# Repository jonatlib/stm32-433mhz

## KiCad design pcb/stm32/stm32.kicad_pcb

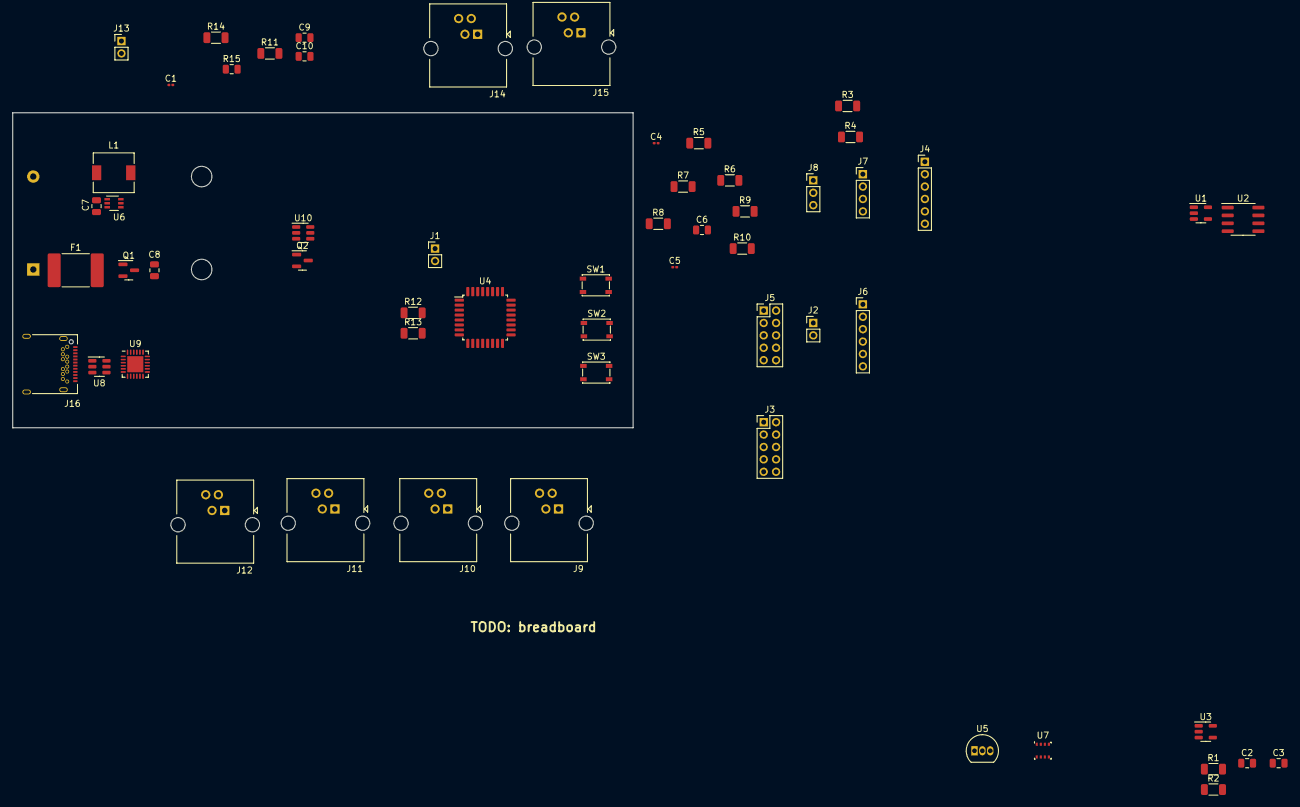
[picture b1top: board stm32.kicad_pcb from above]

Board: 2 copper layers, 100.1 x 50.8 mm, 59 parts (1 on the bottom side), 34 nets, no tracks yet.

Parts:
BT1: Battery; BatteryHolder_Keystone_2462_2xAA
C1: 100n; C_0201_0603Metric
C2, C7, C8, C9: 10u; C_0805_2012Metric
C3, C10: 100n; C_0805_2012Metric
C4, C5: 100nF; C_0201_0603Metric
C6: 1uF; C_0805_2012Metric
F1: Fuse; Fuse_2920_7451Metric_Pad2.10x5.45mm_HandSolder
J1, J2, J13: Conn_01x02_Pin; PinHeader_1x02_P2.00mm_Vertical
J3, J5: Conn_02x05_Top_Bottom; PinHeader_2x05_P2.00mm_Vertical
J4, J6: Conn_01x06_Pin; PinHeader_1x06_P2.00mm_Vertical
J7: Conn_01x04_Pin; PinHeader_1x04_P2.00mm_Vertical
J8: Conn_01x02_Pin; PinHeader_1x03_P2.00mm_Vertical
J9, J10, J11, J12, J14, J15: 4P4C; RJ14_Connfly_DS1133-S4_Horizontal
J16: USB_C_Receptacle; USB_C_Receptacle_Amphenol_12401548E4-2A
L1: 4,7uH; L_6.3x6.3_H3
Q1: ???; SOT-23
Q2: DMG3415; SOT-23
R1, R2, R3, R4, R5, R6, R7, R8, R9: 10K; R_1206_3216Metric
R10: 1K; R_1206_3216Metric
R11: 47k?; R_1206_3216Metric
R12, R13: 500K 1%; R_1206_3216Metric
R14: ?? 1%; R_1206_3216Metric
R15: ?? 1%; C_0805_2012Metric
SW1, SW2, SW3: SW_Push; SW_SPST_PTS810
U1: 24AA02-OT; SOT-23-5
U2: 23A256; SOIC-8_3.9x4.9mm_P1.27mm
U3: TPS2041B; SOT-23-5
U4: STM32G070KBT6; LQFP-32_7x7mm_P0.8mm
U5: DS18B20; TO-92_Inline
U6: TPS61222DCK; Texas_R-PDSO-G6
U7: BME280; Bosch_LGA-8_2.5x2.5mm_P0.65mm_ClockwisePinNumbering
U8: USBLC6-4SC6; SOT-23-6
U9: CP2102N-Axx-xQFN24; QFN-24-1EP_4x4mm_P0.5mm_EP2.6x2.6mm
U10: TPL5110; SOT-23-6

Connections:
5V_Enable: J3.4, R11.1, U4.15 (PB0-GPIO_Output), U6.6 (EN)
+3.3V: C1.1, C4.1, C6.1, C8.1, J1.1, J1.2, J2.1, J4.1, J6.1, J7.1, J8.1, J13.1, Q1.2 (S), R1.1, R2.1, R3.1, R4.1, R5.2, R9.1, R12.1, SW1.1, SW2.1, U1.4 (V_{CC}), U2.7 (~HOLD), U2.8 (VCC), U3.5 (IN), U4.4 (VDD)
+5V: C9.1, C10.1, R14.1, U6.4 (VOUT)
/power_supply/VBAT_SENSE: R12.2, R13.1, U4.12 (PA5-ADC1_IN5)
BOOT0: J5.8, J6.2, R8.1, SW2.2, U4.25 (PA14-BOOT0-SYS_SWCLK)
GND: BT1.2 (-), C1.2, C2.2, C3.2, C4.2, C5.2, C6.2, C7.2, C8.2, C9.2, C10.2, J3.5, J3.10, J4.6, J5.2, J5.7, J6.3, J7.4, J8.3, Q1.1 (G), R6.2, R7.2, R8.2, R11.2, R13.2, R15.2, SW3.2, U1.2 (V_{SS}), U1.5 (WP), U2.4 (VSS), U3.2 (GND), U4.5 (VSS), U6.3 (GND)
I2C_SCL: J3.8, J7.3, R4.2, U1.1 (SCL), U4.30 (PB6-I2C1_SCL)
I2C_SDA: J3.3, J7.2, R3.2, U1.3 (SDA), U4.1 (PB9-I2C1_SDA)
unnamed: C7.1, J13.2, L1.1, U6.1 (VIN)
unnamed: BT1.1 (+), F1.1
unnamed: J2.2, J5.4, J5.9
unnamed: J16.A1 (GND), J16.A12 (GND), J16.B1 (GND), J16.B12 (GND)
unnamed: J16.A4 (VBUS), J16.A9 (VBUS), J16.B4 (VBUS), J16.B9 (VBUS)
unnamed: F1.2, Q1.3 (D)
unnamed: R10.2, SW3.1
unnamed: R2.2, U3.3 (~OC)
unnamed: R14.2, R15.1, U6.2 (FB)
unnamed: L1.2, U6.5 (L)
unnamed: U9.2 (GND), U9.25 (GND)
OneWire: J3.7, R5.1, U4.18 (PA8-GPIO_Output)
RF_RX: J3.1, U4.2 (PC14-OSC32_IN-GPIO_EXTI14)
RF_TX: J3.6, U4.3 (PC15-OSC32_OUT-GPIO_EXTI15)
SENSOR_VDD: C2.1, C3.1, U3.1 (OUT)
SEN_ENABLE: J3.9, R1.2, U3.4 (~EN), U4.16 (PB1-GPIO_Output)
SPI_MISO: J4.3, U2.2 (Q), U4.22 (PA11PA9-SPI1_MISO)
SPI_MOSI: J4.4, U2.5 (D), U4.23 (PA12PA10-SPI1_MOSI)
SPI_SCK: J4.2, U2.6 (C), U4.8 (PA1-SPI1_SCK)
SPI_SS1: U2.1 (~S), U4.13 (PA6-ADC1_IN6)
SPI_SS2: J4.5, U4.14 (PA7-ADC1_IN7)
SWD_IO: J5.6, J6.4, U4.24 (PA13-SYS_SWDIO)
SWD_RESET: C5.1, J5.1, J6.5, R9.2, R10.1, U4.6 (PF2-NRST)
Sleep_Enable: J3.2, U4.17 (PB2-GPIO_Output)
WAKEUP_1: R7.1, U4.7 (PA0-SYS_WKUP1)
WAKEUP_2: J8.2, R6.1, SW1.2, U4.11 (PA4-SYS_WKUP2)

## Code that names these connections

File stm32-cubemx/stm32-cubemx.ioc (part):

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Mcu.Name=STM32G070KBTx
Mcu.Package=LQFP32
Mcu.UserName=STM32G070KBTx
PA0.Mode=SYS_WakeUp0
PA0.Signal=SYS_WKUP1
PA1.Mode=Full_Duplex_Master
PA1.Signal=SPI1_SCK
PA10.Mode=Asynchronous
PA10.Signal=USART1_RX
PA11\ [PA9].Mode=Full_Duplex_Master
PA11\ [PA9].Signal=SPI1_MISO
PA12\ [PA10].Mode=Full_Duplex_Master
PA12\ [PA10].Signal=SPI1_MOSI
PA13.Mode=Serial_Wire
PA13.Signal=SYS_SWDIO
PA14-BOOT0.Mode=Serial_Wire
PA14-BOOT0.Signal=SYS_SWCLK
PA4.Mode=SYS_WakeUp1
PA4.Signal=SYS_WKUP2
PA5.Mode=IN5
PA5.Signal=ADC1_IN5
PA6.Mode=IN6
PA6.Signal=ADC1_IN6
PA7.Mode=IN7
PA7.Signal=ADC1_IN7
PA8.Signal=GPIO_Output
PA9.Mode=Asynchronous
PA9.Signal=USART1_TX
PB0.Signal=GPIO_Output
PB1.Signal=GPIO_Output
PB2.Signal=GPIO_Output
PB6.Mode=I2C
PB6.Signal=I2C1_SCL
PB9.Mode=I2C
PB9.Signal=I2C1_SDA
PC14-OSC32_IN\ (PC14).Signal=GPXTI14
PC15-OSC32_OUT\ (PC15).Signal=GPXTI15
RCC.HSE_VALUE=8000000
RCC.SYSCLKFreq_VALUE=16000000
board=custom

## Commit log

2023-02-04 Better timing handling
2023-02-04 Generic writer and reader
2023-02-04 Cleanup
2023-02-04 Added base reader and writer
2023-02-05 Transport writer working
2023-02-05 Work on packet builder and codec
2023-02-06 Prepared receiving transport
2023-02-06 Renamed address fields not to be confusing
2023-02-06 Implementing window
2023-02-06 Optimistics receiving done
2023-02-06 Simple receiver
2023-02-06 Preparing main structure
2023-02-06 Clippy fixes
2023-02-06 Clippy errors
2023-02-06 Some changes and working reader
2023-02-06 Removed unused traces
2023-02-06 Timing and comments
2023-02-07 Some more comments and cleanups
2023-02-07 Working on HW layer
2023-02-07 Added HAL and builder
2023-02-07 How to resolve the strong reference?
2023-02-07 Linting errors
2023-02-07 It compiles!
2023-02-07 Sending struct
2023-02-07 Added proper sequence numbers
2023-02-07 Prepare for resend
2023-02-08 Moved sequence numbers to a different module
2023-02-08 Working on sequence numbers tests
2023-02-08 WIP ordering
2023-02-08 More tests
2023-02-09 Command for local test
2023-02-09 Finally sequence number working
2023-02-09 Sequence numbers done
2023-02-09 Window implemented using new sequence numbers
2023-02-09 Sorting in window
2023-02-09 Enable resend again
2023-02-09 Main cleanup
2023-02-09 Resend working
2023-02-10 Added create i2c bus
2023-02-10 Updated compile flags
2023-02-10 Testing shorter timing
2023-02-12 Preparing manufacturing
2023-02-13 Adding sensor dependencies
2023-02-13 Preparing schema
2023-02-13 Fixed schema
2023-02-14 Upgrade to kicad7
2023-02-14 Prepared labels for MCU
2023-02-15 PCB update
2023-02-17 PCB stuff
2023-02-17 Slow progress
2023-02-17 Updated PCB
2023-02-19 Update pcb
2023-02-20 Preparing new codecs
2023-02-20 WIP reed solomon
2023-02-20 Dynamic size for codec
2023-02-20 Reed solomon codec
2023-02-20 Using different codec
2023-02-21 Const reed solomon buffer size
2023-02-21 Reed solomon buffers are now generic
2023-02-21 RS tests
2023-02-21 Preparing chaining
2023-02-21 Support for codec errors
2023-02-21 Chain WIP
2023-02-21 Codecs
2023-02-21 WIP compression
2023-02-21 Fixed compression
2023-02-22 WIP compression in writer
2023-02-22 Finished compression in writer side
2023-02-22 Use reedsolomon and compression in main
2023-02-22 Support decompression
2023-02-22 Make it compilable
2023-02-22 Implemented chaining
2023-02-22 Four to six bits
2023-02-22 Use RS and 4/6 codec at the same time
2023-02-22 Some fixes on HW
2023-02-25 Playing with memoery
2023-02-25 Added all hiearchical labels
2023-02-26 Updated in memory
2023-02-26 Prepare for other components
2023-02-27 More work on memory
2023-02-27 Refactor modules
2023-02-27 Dummy memory
2023-02-27 Test
2023-02-28 WIP allocator
2023-02-28 Generic memory
2023-02-28 FIX memory typing
2023-02-28 Screw generic memory
2023-02-28 Dummy executor
2023-02-28 Tests for box
2023-02-28 Testing custom box
2023-02-28 Added available memory fns
2023-02-28 Allocator fixes
2023-02-28 Collapse
2023-03-01 Collapsing
2023-03-01 Fixed lifetimes
2023-03-01 Support for generic cold array
2023-03-01 Renamed to ColdBox
2023-03-01 WIP vec
2023-03-01 Moved boxed to more modules
2023-03-01 API to work with smaller memory then allocated
2023-03-01 Array access on box
2023-03-01 Cold vec
2023-03-02 Small fixes
2023-03-03 Power supply
2023-03-03 Vec progress
2023-03-03 From iterator
2023-03-03 Moved PCB forwar
2023-03-03 Packages
2023-03-03 PCB testing
2023-03-06 VDD supply added
2023-03-06 PCB updates
2023-03-06 PWR comment
2023-03-07 updated power supply comment
2023-03-07 PCB in progress
2023-03-07 Progress
2023-03-08 Setup board
2023-03-08 Setup traces
2023-03-08 Updated tracks in PCB
2023-03-09 Small work on pcb
2023-03-09 Global allocator
2023-03-09 Support from iter in vec with global allocator
2023-03-10 unsafe sync on dummy allocator for testing
2023-03-10 Added test for from iter
2023-03-10 Fixing global allocator
2023-03-13 Testing the allocator memory addresses
2023-03-13 Fixed from iter
2023-03-14 Fixing global allocator init
2023-03-14 Moved global alloc tests
2023-03-17 WIP pcb
2023-04-07 Small update
2023-04-08 Added todos
2023-04-11 Renamed PWM reader and writer
2023-04-11 WIP manchester
2023-04-11 Moved all pwm physical layer under under submodule
2023-04-11 Clippy for external memory
2023-04-11 Clippy base fixes
2023-04-11 Renamed bit_io to physical_layer
2023-04-11 update schema
2023-04-12 Small updates on pcb
2023-06-01 Fixing for new version of rust
2023-06-02 Preparing separated sync
2023-06-03 Prearing syncing
2023-06-06 Removed wrong RefCells
2023-06-06 WIP container for clonning
2023-06-07 WIP shared
2023-06-07 WIP shared pin
2023-06-07 Finished shared pin for readers
2023-06-07 Implemnted shared output and sync writer
2023-06-08 Starting manchester
2023-06-08 WIP manchester read
2023-06-09 Finished a weird manchester writer
2023-06-10 Testing Manchester writer
2023-06-11 Custom manchester writer
2023-06-11 Custom manchester reader
2023-06-11 Not working manchester encoding... figure out why
2023-06-11 Now we should test the manchester codec if it is even working
2023-06-12 Moved manchester to separate package
2023-06-13 Tests for 322
2023-06-14 Fixed manchester coding with tests
2023-06-14 Added some timouets so readed can reset
2023-06-14 Preparing Packet64
2023-06-14 Longer sync sequence
2023-06-14 Preparation for 64bits packets CRC4 computation
2023-06-15 Make HW in physical layer as feature and enable testing in network
2023-06-15 Test for crc4
2023-06-15 Split packet builder to two builders by packet size
2023-06-15 WIP support for switching packet type
2023-06-15 Should work for packet32
2023-06-15 Not working Packet32 after changes to 64
2023-06-16 Maybe a hotfix to window and packet sizes
2023-06-16 WIP to get network tests working with defmt printing
2023-06-16 Sealed not working output from defmt in tests
2023-06-16 Check what is wrong with packet type conversion
2023-06-16 Tests for u64 into 32packet
2023-06-16 Same interface for both packets
2023-06-16 Working tests with loggin
2023-06-16 Working test on something that does not work on HW
2023-06-16 Test with multiple packets
2023-06-16 Fixed based on test for networking
2023-06-16 Receiver working tests for all kind of packets
2023-06-16 Finished packet builder for 64bit packets
2023-06-16 Moved everything from BE to LE
2023-06-16 Hotfix packet32; 64 still not working, packets are correct but payload is wrong from packet
2023-06-19 WIP stream ID to drop invalid packet from different stream
2023-06-19 Moved packet sizes to constant in a single module
2023-06-19 Impemented usage of stream ids
2023-06-19 Fix tests for packet32
2023-06-19 This is working on HW
2023-06-19 Codecs are not working
2023-06-23 WIP better network testing
2023-06-23 Fixed testing lifetimes
2023-06-23 Working network full test
2023-06-23 Almost working intyegration test
2023-06-24 Working integration test
2023-06-24 Working with tests on HW
2023-06-26 Better network testing
2023-06-26 FIXME comment in testing
2023-06-30 Added full tests for networking
2023-06-30 TODO tests for packet 64
